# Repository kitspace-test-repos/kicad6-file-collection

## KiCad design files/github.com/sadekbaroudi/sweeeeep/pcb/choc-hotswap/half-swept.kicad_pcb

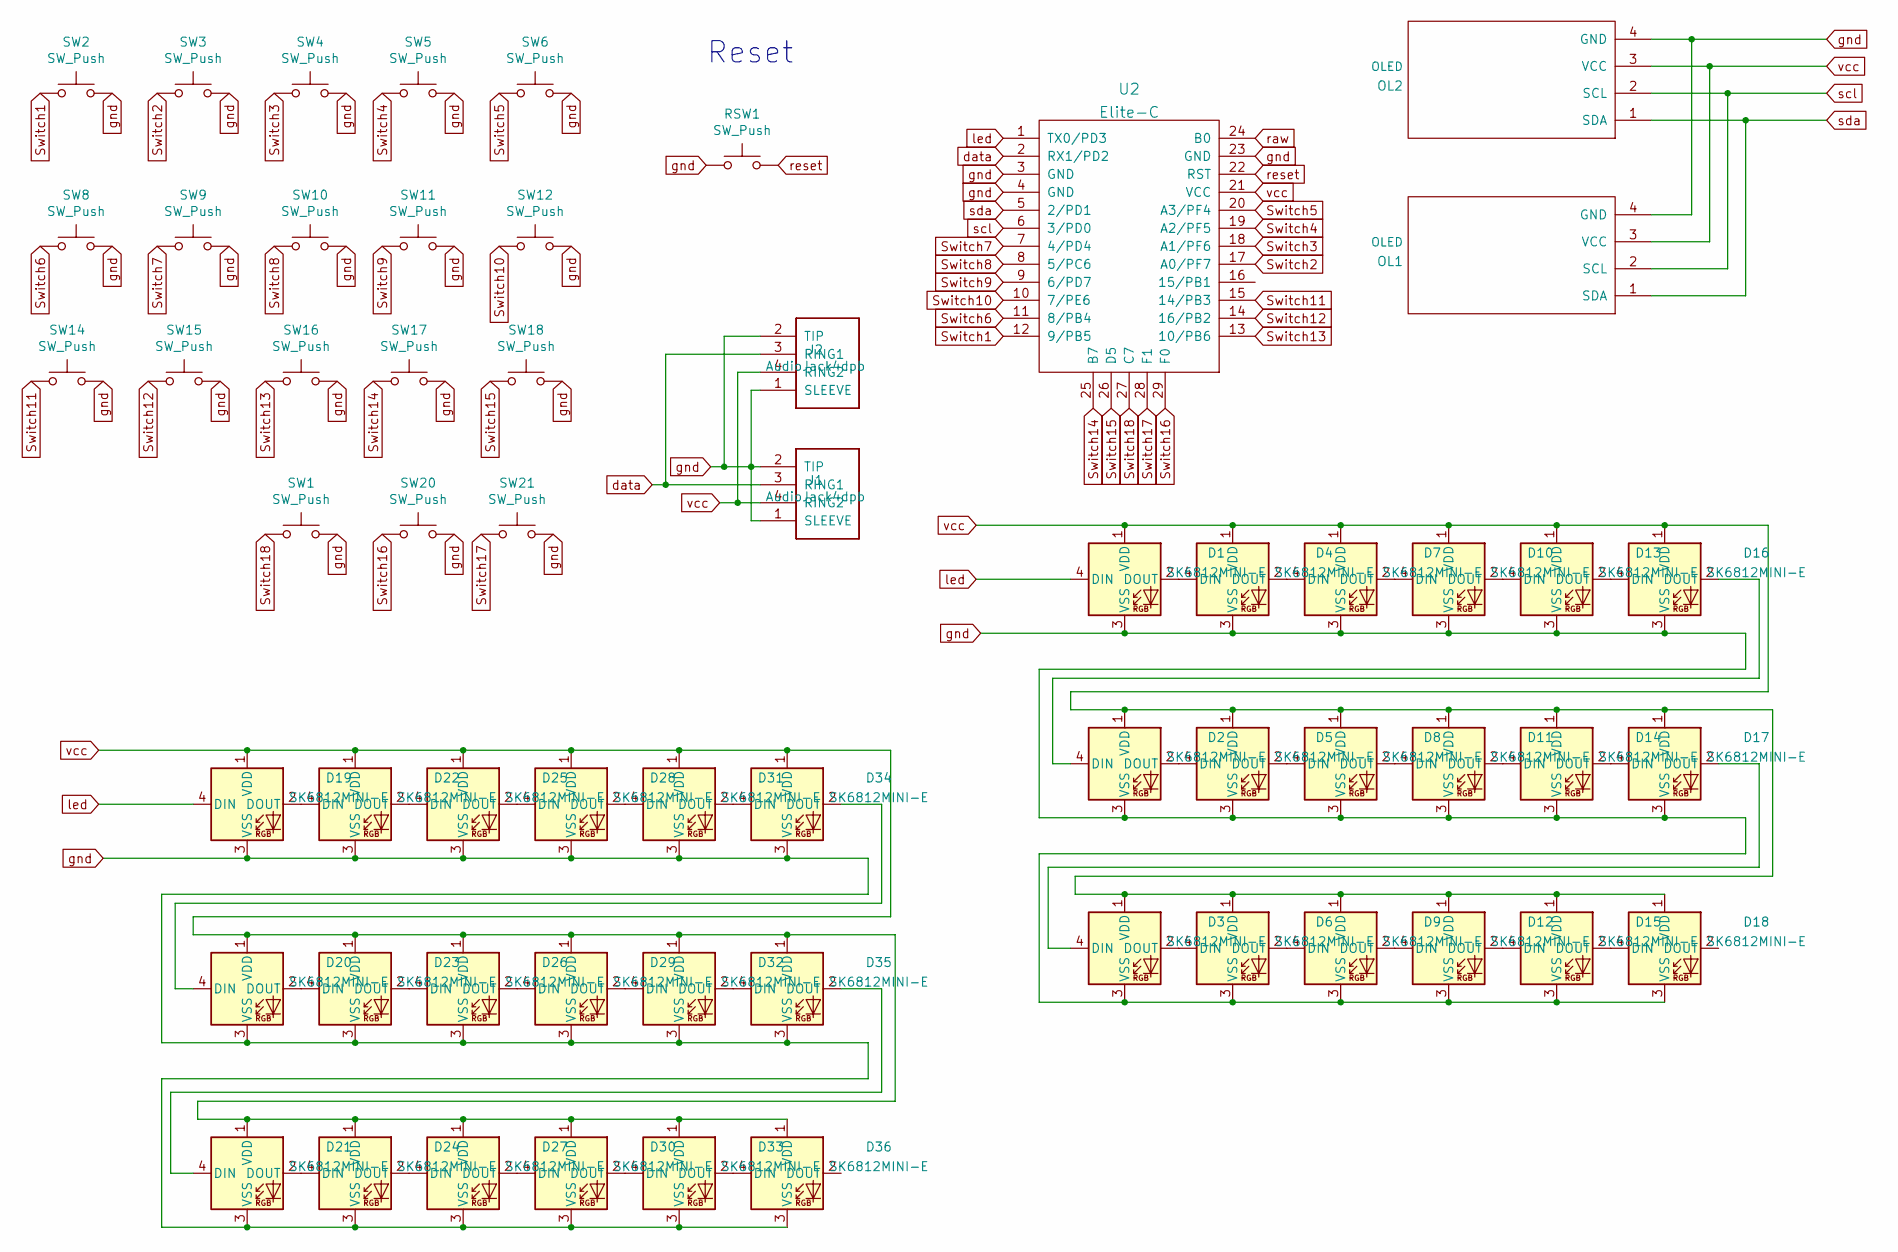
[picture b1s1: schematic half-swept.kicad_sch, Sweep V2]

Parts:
D1, D2, D3, D4, D5, D6, D7, D8, D9, D10, D11, D12, D13, D14, D15, D16, D17, D18, D19, D20, D21, D22, D23, D24, D25, D26, D27, D28, D29, D30, D31, D32, D33, D34, D35, D36: SK6812MINI-E; MX_SK6812MINI-E_REV
J1, J2: AudioJack4dpb; TRRS-PJ-320A
OL1, OL2: OLED; OLED_v2
RSW1: SW_Push; SW_Tactile_SPST_Angled_MJTP1117-no-mount
SW1, SW2, SW3, SW4, SW5, SW6, SW8, SW9, SW10, SW11, SW12, SW14, SW15, SW16, SW17, SW18, SW20, SW21: SW_Push; Kailh_socket_PG1350_reversible
U2: Elite-C

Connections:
unnamed: D1.2 (DOUT), D4.4 (DIN)
unnamed: D2.2 (DOUT), D5.4 (DIN)
unnamed: D3.2 (DOUT), D6.4 (DIN)
unnamed: D4.2 (DOUT), D7.4 (DIN)
unnamed: D5.2 (DOUT), D8.4 (DIN)
unnamed: D6.2 (DOUT), D9.4 (DIN)
unnamed: D10.2 (DOUT), D13.4 (DIN)
unnamed: D7.2 (DOUT), D10.4 (DIN)
unnamed: D11.2 (DOUT), D14.4 (DIN)
unnamed: D8.2 (DOUT), D11.4 (DIN)
unnamed: D12.2 (DOUT), D15.4 (DIN)
unnamed: D9.2 (DOUT), D12.4 (DIN)
unnamed: D13.2 (DOUT), D16.4 (DIN)
unnamed: D14.2 (DOUT), D17.4 (DIN)
unnamed: D15.2 (DOUT), D18.4 (DIN)
unnamed: D2.4 (DIN), D16.2 (DOUT)
unnamed: D3.4 (DIN), D17.2 (DOUT)
unnamed: D19.2 (DOUT), D22.4 (DIN)
unnamed: D20.2 (DOUT), D23.4 (DIN)
unnamed: D20.4 (DIN), D34.2 (DOUT)
unnamed: D21.2 (DOUT), D24.4 (DIN)
unnamed: D21.4 (DIN), D35.2 (DOUT)
unnamed: D22.2 (DOUT), D25.4 (DIN)
unnamed: D23.2 (DOUT), D26.4 (DIN)
unnamed: D24.2 (DOUT), D27.4 (DIN)
unnamed: D25.2 (DOUT), D28.4 (DIN)
unnamed: D26.2 (DOUT), D29.4 (DIN)
unnamed: D27.2 (DOUT), D30.4 (DIN)
unnamed: D28.2 (DOUT), D31.4 (DIN)
unnamed: D29.2 (DOUT), D32.4 (DIN)
unnamed: D30.2 (DOUT), D33.4 (DIN)
unnamed: D31.2 (DOUT), D34.4 (DIN)
unnamed: D32.2 (DOUT), D35.4 (DIN)
unnamed: D33.2 (DOUT), D36.4 (DIN)
Switch1: SW2.1, U2.12 (9/PB5)
Switch2: SW3.1, U2.17 (A0/PF7)
Switch3: SW4.1, U2.18 (A1/PF6)
Switch4: SW5.1, U2.19 (A2/PF5)
Switch5: SW6.1, U2.20 (A3/PF4)
Switch6: SW8.1, U2.11 (8/PB4)
Switch7: SW9.1, U2.7 (4/PD4)
Switch8: SW10.1, U2.8 (5/PC6)
Switch9: SW11.1, U2.9 (6/PD7)
Switch10: SW12.1, U2.10 (7/PE6)
Switch11: SW14.1, U2.15 (14/PB3)
Switch12: SW15.1, U2.14 (16/PB2)
Switch13: SW16.1, U2.13 (10/PB6)
Switch14: SW17.1, U2.25 (B7)
Switch15: SW18.1, U2.26 (D5)
Switch16: SW20.1, U2.29 (F0)
Switch17: SW21.1, U2.28 (F1)
Switch18: SW1.1, U2.27 (C7)
data: J1.3 (RING1), J2.3 (RING1), U2.2 (RX1/PD2)
gnd: D1.3 (VSS), D2.3 (VSS), D3.3 (VSS), D4.3 (VSS), D5.3 (VSS), D6.3 (VSS), D7.3 (VSS), D8.3 (VSS), D9.3 (VSS), D10.3 (VSS), D11.3 (VSS), D12.3 (VSS), D13.3 (VSS), D14.3 (VSS), D15.3 (VSS), D16.3 (VSS), D17.3 (VSS), D18.3 (VSS), D19.3 (VSS), D20.3 (VSS), D21.3 (VSS), D22.3 (VSS), D23.3 (VSS), D24.3 (VSS), D25.3 (VSS), D26.3 (VSS), D27.3 (VSS), D28.3 (VSS), D29.3 (VSS), D30.3 (VSS), D31.3 (VSS), D32.3 (VSS), D33.3 (VSS), D34.3 (VSS), D35.3 (VSS), D36.3 (VSS), J1.1 (SLEEVE), J1.2 (TIP), J2.1 (SLEEVE), J2.2 (TIP), OL1.4 (GND), OL2.4 (GND), RSW1.1, SW1.2, SW2.2, SW3.2, SW4.2, SW5.2, SW6.2, SW8.2, SW9.2, SW10.2, SW11.2, SW12.2, SW14.2, SW15.2, SW16.2, SW17.2, SW18.2, SW20.2, SW21.2, U2.3 (GND), U2.4 (GND), U2.23 (GND)
led: D1.4 (DIN), D19.4 (DIN), U2.1 (TX0/PD3)
raw: U2.24 (B0)
reset: RSW1.2, U2.22 (RST)
scl: OL1.2 (SCL), OL2.2 (SCL), U2.6 (3/PD0)
sda: OL1.1 (SDA), OL2.1 (SDA), U2.5 (2/PD1)
vcc: D1.1 (VDD), D2.1 (VDD), D3.1 (VDD), D4.1 (VDD), D5.1 (VDD), D6.1 (VDD), D7.1 (VDD), D8.1 (VDD), D9.1 (VDD), D10.1 (VDD), D11.1 (VDD), D12.1 (VDD), D13.1 (VDD), D14.1 (VDD), D15.1 (VDD), D16.1 (VDD), D17.1 (VDD), D18.1 (VDD), D19.1 (VDD), D20.1 (VDD), D21.1 (VDD), D22.1 (VDD), D23.1 (VDD), D24.1 (VDD), D25.1 (VDD), D26.1 (VDD), D27.1 (VDD), D28.1 (VDD), D29.1 (VDD), D30.1 (VDD), D31.1 (VDD), D32.1 (VDD), D33.1 (VDD), D34.1 (VDD), D35.1 (VDD), D36.1 (VDD), J1.4 (RING2), J2.4 (RING2), OL1.3 (VCC), OL2.3 (VCC), U2.21 (VCC)

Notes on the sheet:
Reset

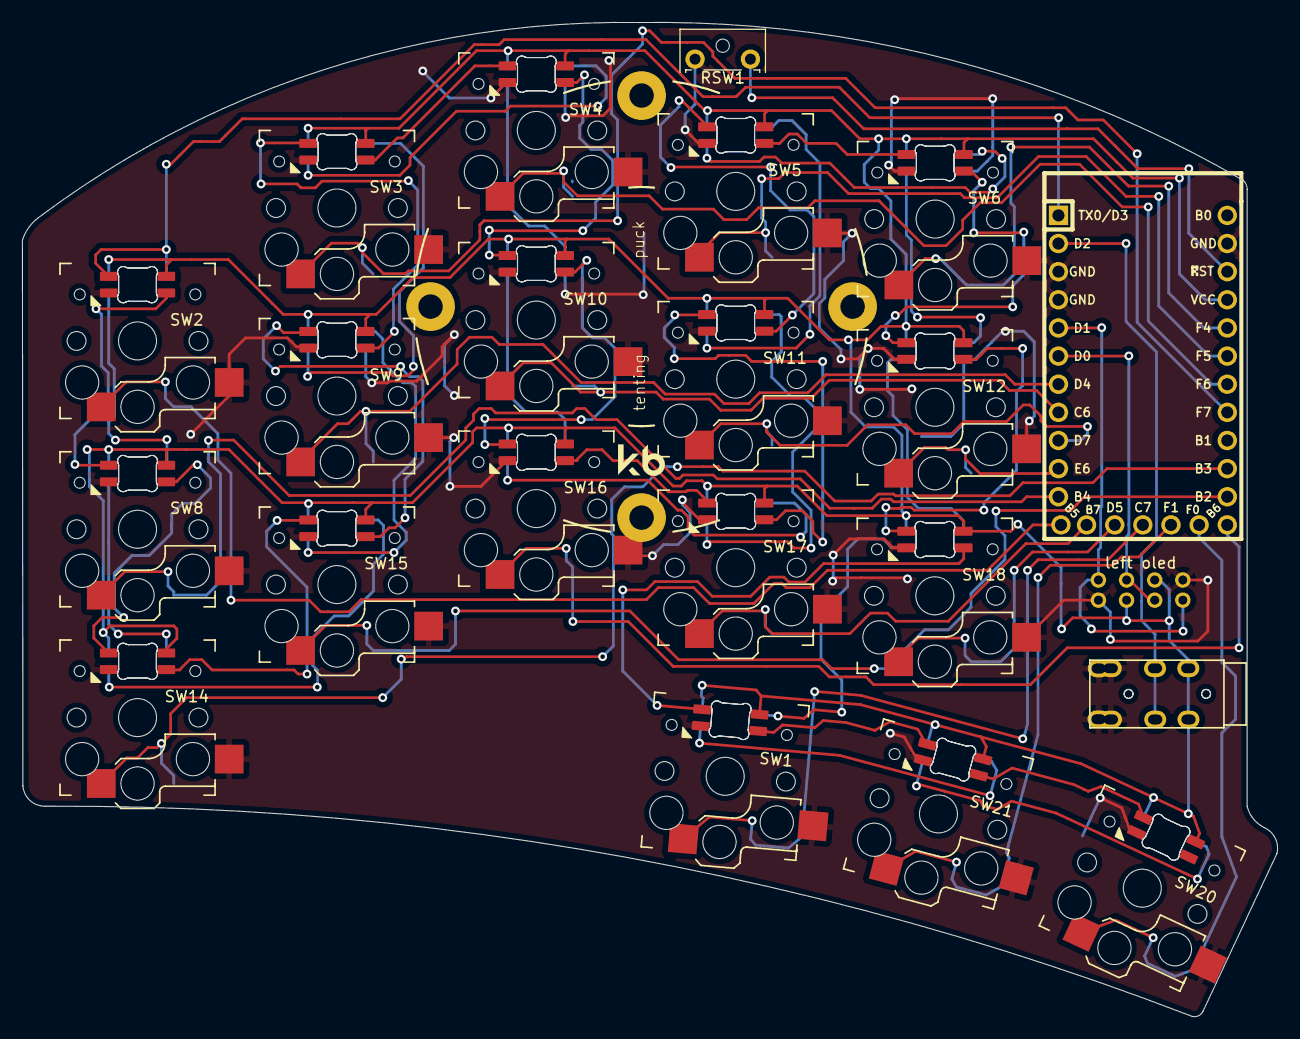
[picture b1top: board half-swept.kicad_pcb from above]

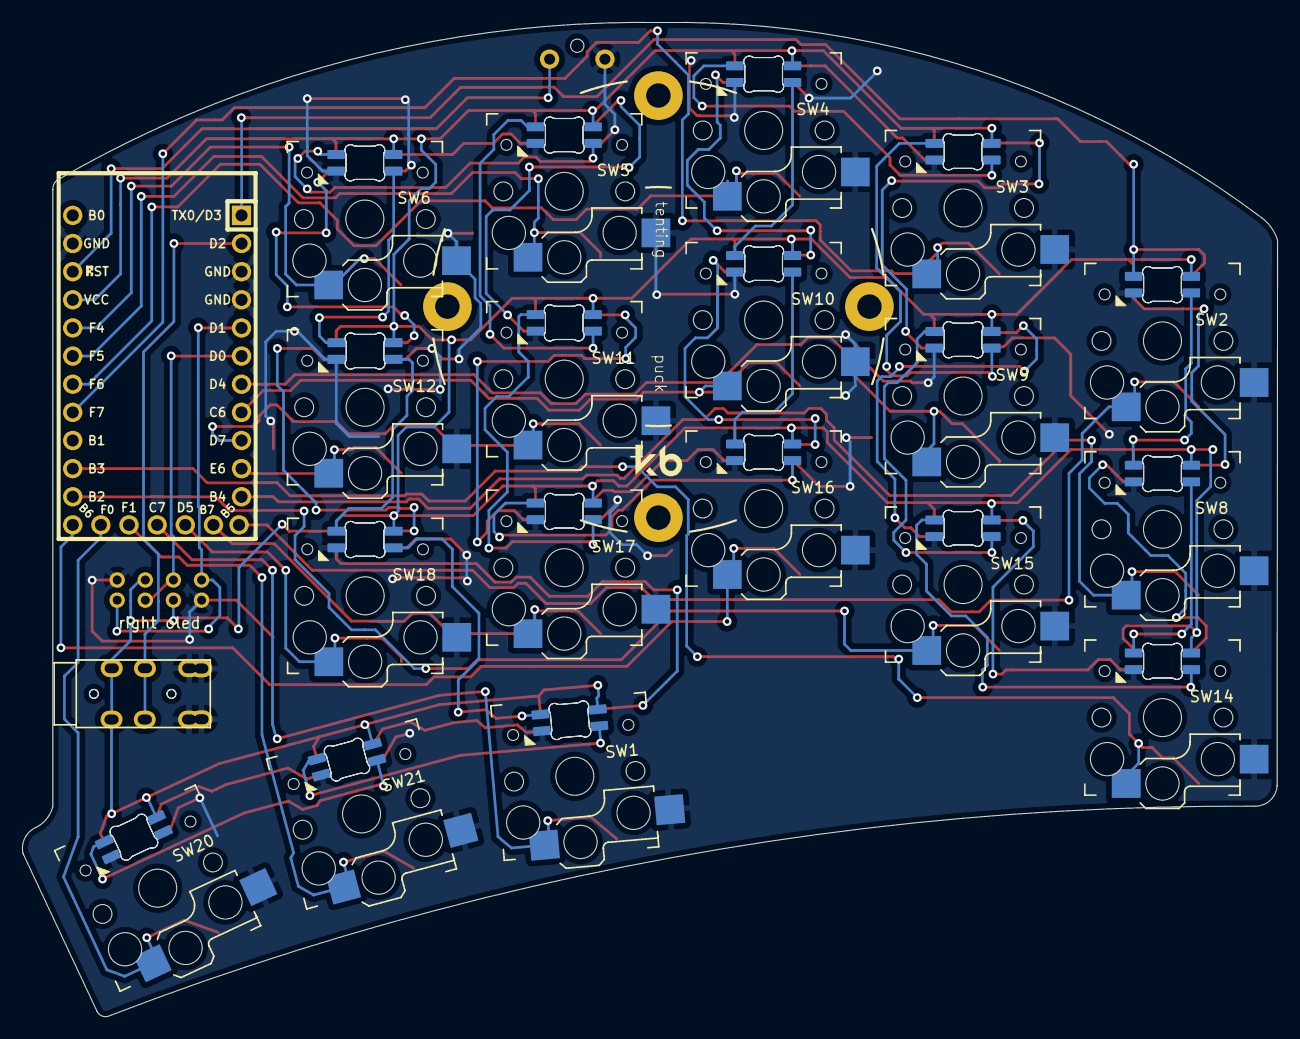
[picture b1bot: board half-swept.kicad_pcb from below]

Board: 2 copper layers, 113.3 x 89.7 mm, 60 parts (20 on the bottom side), 59 nets.

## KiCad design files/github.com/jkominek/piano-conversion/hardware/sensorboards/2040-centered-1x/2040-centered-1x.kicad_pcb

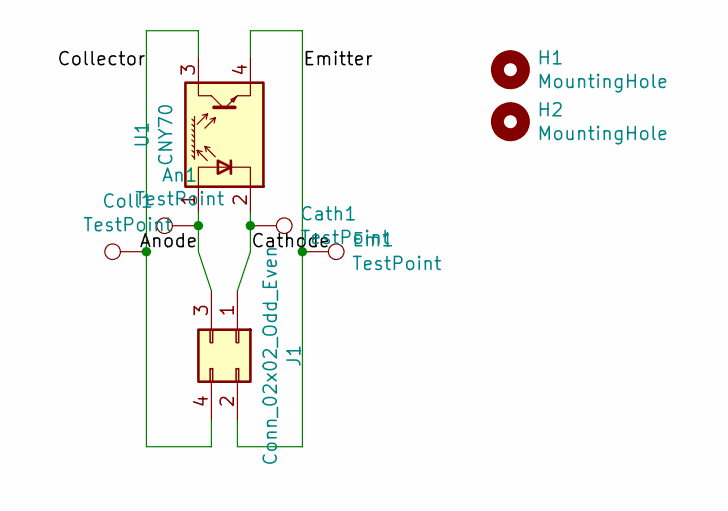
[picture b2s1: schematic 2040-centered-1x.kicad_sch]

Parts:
An1: TestPoint; TestPoint_Pad_1.0x1.0mm
Cath1: TestPoint; TestPoint_Pad_1.0x1.0mm
Coll1: TestPoint; TestPoint_Pad_1.0x1.0mm
Em1: TestPoint; TestPoint_Pad_1.0x1.0mm
H1, H2: MountingHole; MountingHole_3.2mm_M3
J1: Conn_02x02_Odd_Even; Pin_Header_Angled_2x02_Pitch2.54mm
U1: CNY70; Vishay_CNY70

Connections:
/Anode: An1.1, J1.3, U1.1 (A)
/Cathode: Cath1.1, J1.1, U1.2 (K)
/Collector: Coll1.1, J1.4, U1.3 (C)
/Emitter: Em1.1, J1.2, U1.4 (E)

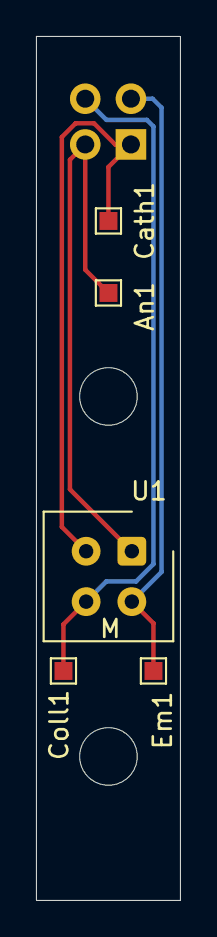
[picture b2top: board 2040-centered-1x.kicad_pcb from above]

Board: 2 copper layers, 8.0 x 48.0 mm, 8 parts (1 on the bottom side), 4 nets.

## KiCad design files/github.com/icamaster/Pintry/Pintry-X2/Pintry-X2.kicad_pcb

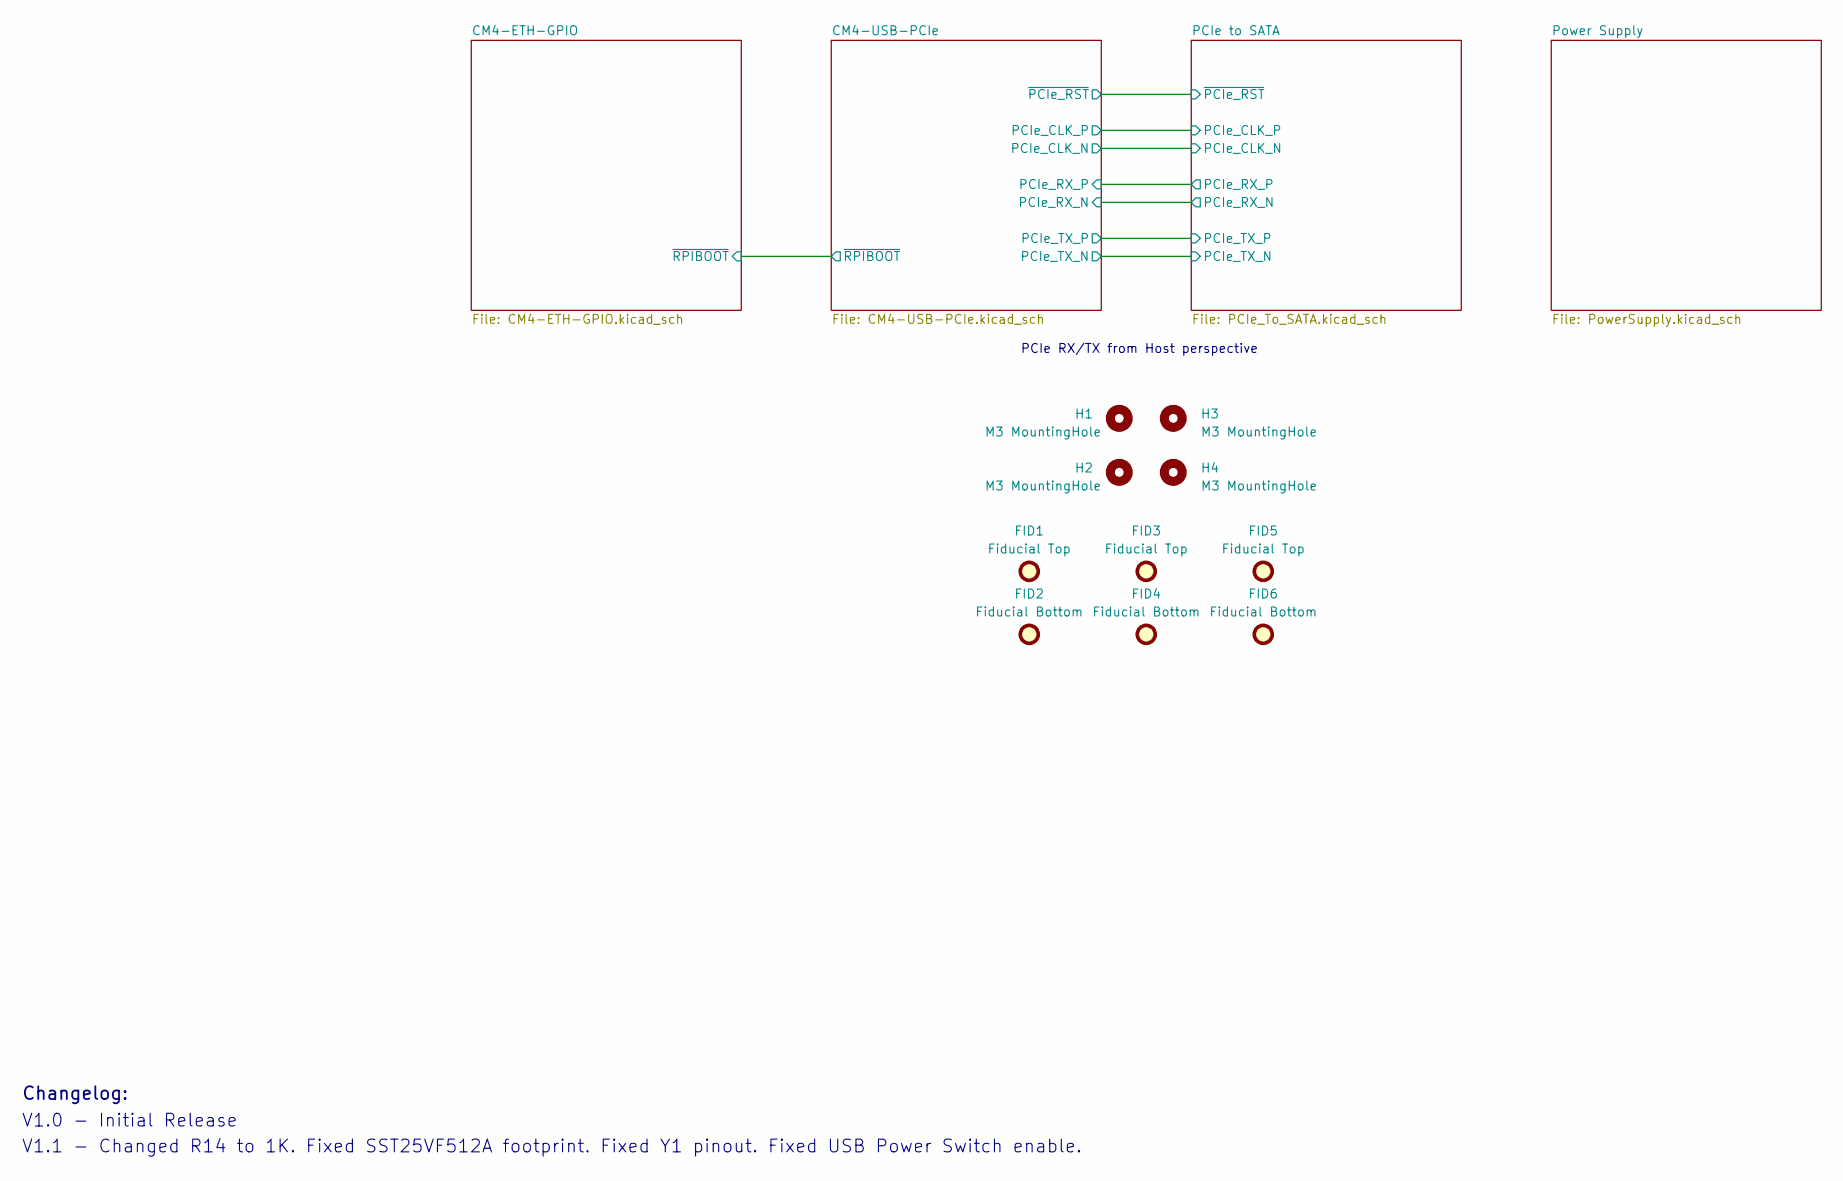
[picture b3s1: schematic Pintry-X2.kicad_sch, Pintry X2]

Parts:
FID1, FID3, FID5: Fiducial Top; Fiducial_1mm_Mask2mm
FID2, FID4, FID6: Fiducial Bottom; Fiducial_1mm_Mask2mm
H1, H2, H3, H4: M3 MountingHole; MountingHole_3.2mm_M3

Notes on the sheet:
V1.0 - Initial Release
Changelog:
PCIe RX/TX from Host perspective
V1.1 - Changed R14 to 1K. Fixed SST25VF512A footprint. Fixed Y1 pinout. Fixed USB Power Switch enable.

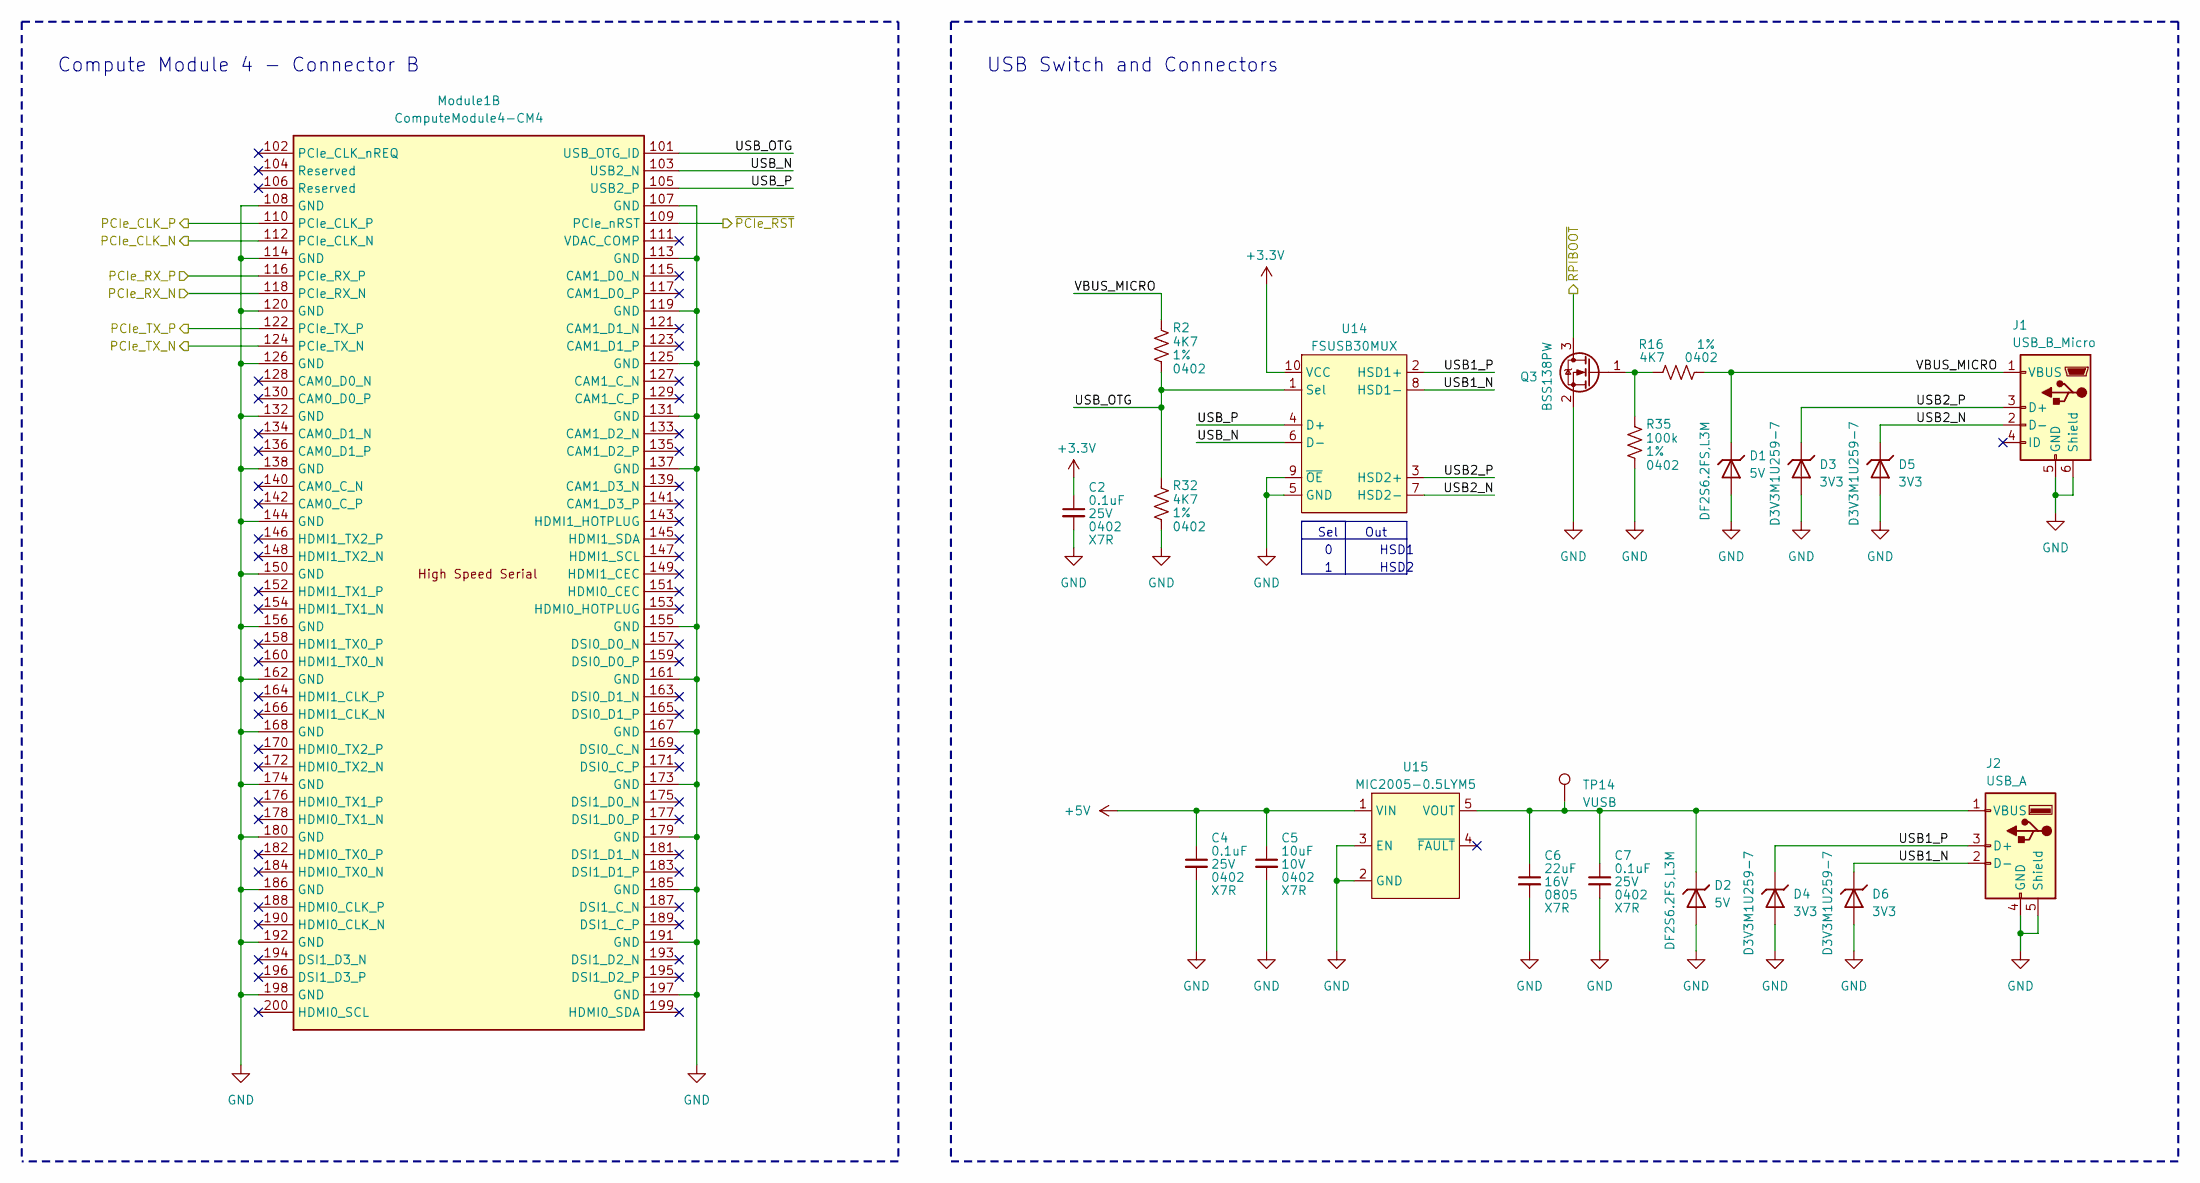
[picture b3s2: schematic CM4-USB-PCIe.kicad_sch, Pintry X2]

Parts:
C2, C4, C7: 0.1uF; C_0402_1005Metric; Voltage Rating 25V
C5: 10uF; C_0402_1005Metric; Voltage Rating 10V
C6: 22uF; C_0805_2012Metric; Voltage Rating 16V; Part Number GRM21BR61A226ME51L
D1, D2: DF2S6.2FS,L3M; D_SOD-923; Part Number DF2S6.2FS,L3M
D3, D4, D5, D6: D3V3M1U259-7; D_SOD-923; Part Number D3V3M1U2S9-7
J1: USB_B_Micro; USB_Micro-B_Amphenol_10103594-0001LF_Horizontal; Part Number 10103594-0001LF
J2: USB_A; USB_A_Amphenol_ICC_73725-11A0BLF_Horizontal; Part Number 73725-11A0BLF
Module1: ComputeModule4-CM4; Raspberry-Pi-4-Compute-Module; Part Number 2x DF40C-100DS-0.4V
Q3: BSS138PW; SOT-323_SC-70; Part Number BSS138PW,115
R2, R16, R32: 4K7; R_0402_1005Metric; Tolerance 1%
R35: 100k; R_0402_1005Metric; Tolerance 1%
TP14: VUSB; TestPoint_Pad_D1.0mm
U14: FSUSB30MUX; MSOP-10_3x3mm_P0.5mm; Part Number FSUSB30MUX
U15: MIC2005-0.5LYM5; SOT-23-5; Part Number MIC2005-0.5LYM5

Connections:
+3V3: C2.1, U14.10 (VCC); also elsewhere on the board
+5V: C4.1, C5.1, U15.1 (VIN); also elsewhere on the board
/CM4-ETH-GPIO/~RPIBOOT: Q3.3 (D); also elsewhere on the board
/CM4-USB-PCIe/PCIe_CLK_N: Module1.112 (PCIe_CLK_N); also elsewhere on the board
/CM4-USB-PCIe/PCIe_CLK_P: Module1.110 (PCIe_CLK_P); also elsewhere on the board
/CM4-USB-PCIe/PCIe_RX_N: Module1.118 (PCIe_RX_N); also elsewhere on the board
/CM4-USB-PCIe/PCIe_RX_P: Module1.116 (PCIe_RX_P); also elsewhere on the board
/CM4-USB-PCIe/PCIe_TX_N: Module1.124 (PCIe_TX_N); also elsewhere on the board
/CM4-USB-PCIe/PCIe_TX_P: Module1.122 (PCIe_TX_P); also elsewhere on the board
/CM4-USB-PCIe/USB1_N: D6.1 (K), J2.2 (D-), U14.8 (HSD1-)
/CM4-USB-PCIe/USB1_P: D4.1 (K), J2.3 (D+), U14.2 (HSD1+)
/CM4-USB-PCIe/USB2_N: D5.1 (K), J1.2 (D-), U14.7 (HSD2-)
/CM4-USB-PCIe/USB2_P: D3.1 (K), J1.3 (D+), U14.3 (HSD2+)
/CM4-USB-PCIe/USB_N: Module1.103 (USB2_N), U14.6 (D-)
/CM4-USB-PCIe/USB_OTG: Module1.101 (USB_OTG_ID), R2.2, R32.1, U14.1 (Sel)
/CM4-USB-PCIe/USB_P: Module1.105 (USB2_P), U14.4 (D+)
/CM4-USB-PCIe/VBUS_MICRO: D1.1 (K), J1.1 (VBUS), R2.1, R16.2
/CM4-USB-PCIe/~PCIe_RST: Module1.109 (PCIe_nRST); also elsewhere on the board
GND: C2.2, C4.2, C5.2, C6.2, C7.2, D1.2 (A), D2.2 (A), D3.2 (A), D4.2 (A), D5.2 (A), D6.2 (A), J1.5 (GND), J1.6 (Shield), J2.4 (GND), J2.5 (Shield), Module1.107 (GND), Module1.108 (GND), Module1.113 (GND), Module1.114 (GND), Module1.119 (GND), Module1.120 (GND), Module1.125 (GND), Module1.126 (GND), Module1.131 (GND), Module1.132 (GND), Module1.137 (GND), Module1.138 (GND), Module1.144 (GND), Module1.150 (GND), Module1.155 (GND), Module1.156 (GND), Module1.161 (GND), Module1.162 (GND), Module1.167 (GND), Module1.168 (GND), Module1.173 (GND), Module1.174 (GND), Module1.179 (GND), Module1.180 (GND), Module1.185 (GND), Module1.186 (GND), Module1.191 (GND), Module1.192 (GND), Module1.197 (GND), Module1.198 (GND), Q3.2 (S), R32.2, R35.2, U14.5 (GND), U14.9 (~OE), U15.2 (GND), U15.3 (EN); also elsewhere on the board
unnamed: C6.1, C7.1, D2.1 (K), J2.1 (VBUS), TP14.1, U15.5 (VOUT)
unnamed: Q3.1 (G), R16.1, R35.1

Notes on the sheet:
Compute Module 4 - Connector B
Sel Out
USB Switch and Connectors
1 HSD2
0 HSD1

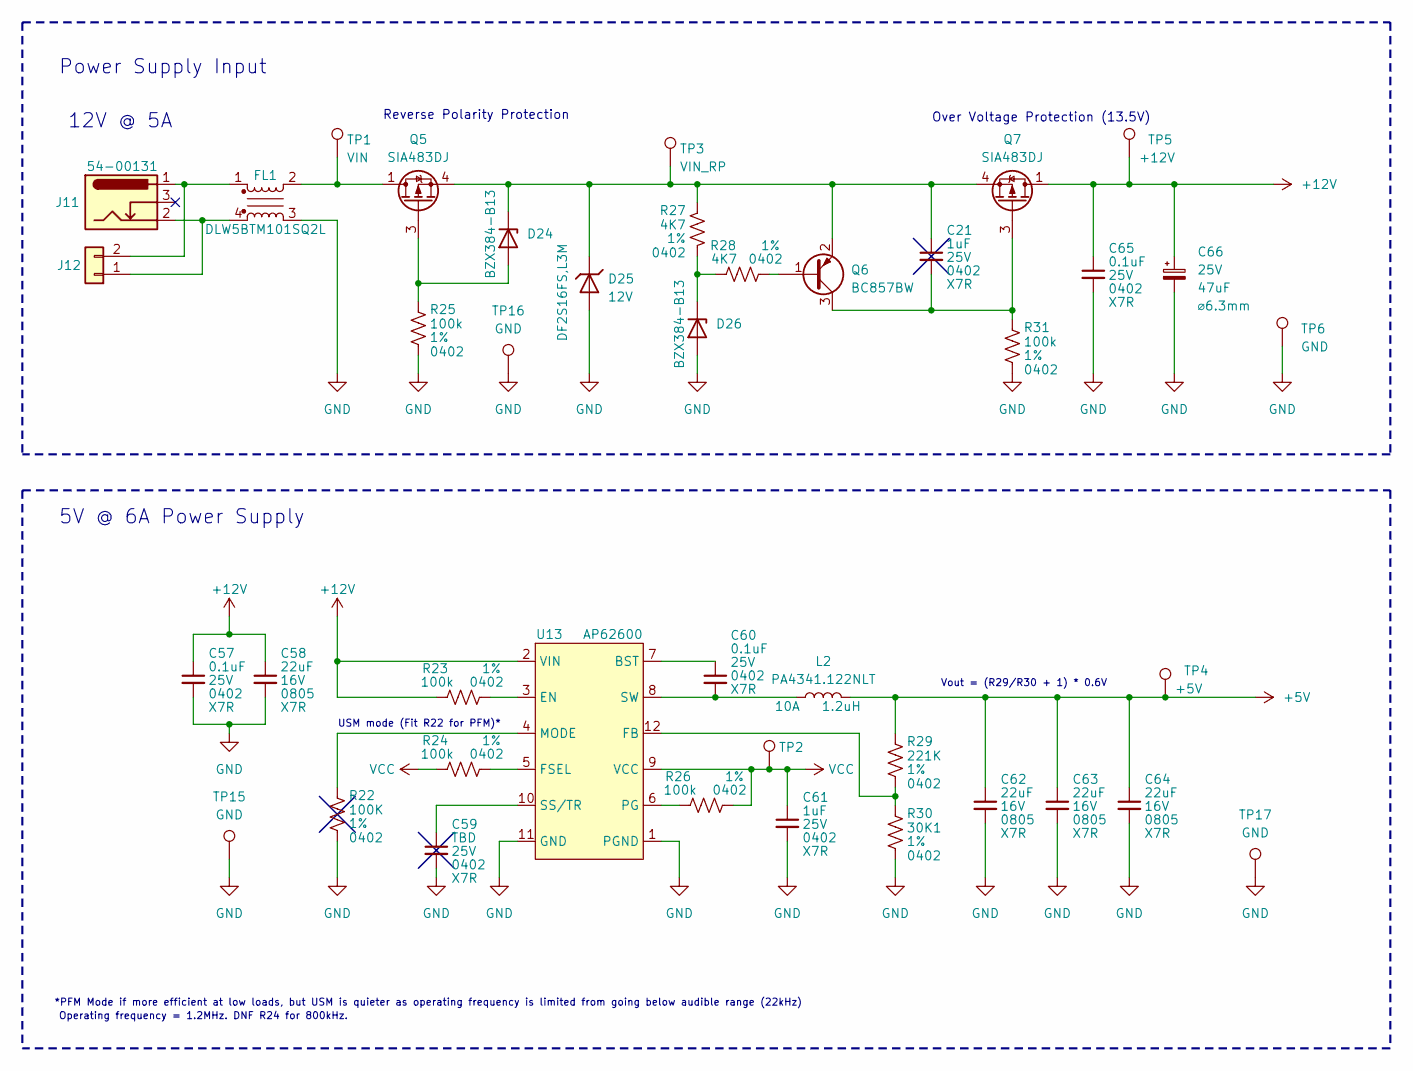
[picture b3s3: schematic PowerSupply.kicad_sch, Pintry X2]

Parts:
C21, C61: 1uF; C_0402_1005Metric; Voltage Rating 25V
C57, C60, C65: 0.1uF; C_0402_1005Metric; Voltage Rating 25V
C58: 22uF; C_0805_2012Metric; Voltage Rating 16V; Part Number CL21A226MOQNNNE
C59: TBD; C_0402_1005Metric; Voltage Rating 25V
C62, C63, C64: 22uF; C_0805_2012Metric; Voltage Rating 16V; Part Number GRM21BR61A226ME51L
C66: 865080443007; CP_Elec_6.3x5.4; Voltage 25V; Part Number 865080443007
D24, D26: BZX384-B13; D_SOD-323; Part Number BZX384-B13,115
D25: DF2S16FS,L3M; D_SOD-923; Part Number DF2S16FS,L3M
FL1: DLW5BTM101SQ2L; Part Number DLW5BTM101SQ2L
J11: 54-00131; Part Number 54-00131
J12: Alternate Power Connector; SolderWire-1sqmm_1x02_P5.4mm_D1.4mm_OD2.7mm
L2: PA4341.122NLT; Pulse_PA4341; Current Rating 10A; Part Number PA4341.122NLT
Q5, Q7: SIA483DJ; Vishay_PowerPAK_SC70-6L_Single; PartNumber SIA483DJ-T1-GE3
Q6: BC857BW; SOT-323_SC-70; Part Number BC857BW,135
R22: 100K; R_0402_1005Metric; Tolerance 1%
R23, R24, R25, R26, R31: 100k; R_0402_1005Metric; Tolerance 1%
R27, R28: 4K7; R_0402_1005Metric; Tolerance 1%
R29: 221K; R_0402_1005Metric; Tolerance 1%
R30: 30K1; R_0402_1005Metric; Tolerance 1%
TP1: VIN; TestPoint_Pad_D1.0mm
TP2: VCC; TestPoint_Pad_D1.0mm
TP3: VIN_RP; TestPoint_Pad_D1.0mm
TP4: +5V; TestPoint_Pad_D1.0mm
TP5: +12V; TestPoint_Pad_D1.0mm
TP6, TP15, TP16, TP17: GND; TestPoint_Pad_D1.0mm
U13: AP62600; V-QFN2030-12 (Type A); Part Number AP62600SJ-7

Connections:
+5V: C62.1, C63.1, C64.1, L2.2, R29.1, TP4.1; also elsewhere on the board
+12V: C57.1, C58.1, C65.1, C66.1, Q7.1 (D), R23.1, TP5.1, U13.2 (VIN); also elsewhere on the board
GND: C57.2, C58.2, C59.2, C61.2, C62.2, C63.2, C64.2, C65.2, C66.2, D25.2 (A), D26.2 (A), FL1.3, R22.2, R25.2, R30.2, R31.2, TP6.1, TP15.1, TP16.1, TP17.1, U13.1 (PGND), U13.11 (GND); also elsewhere on the board
unnamed: C21.1, D24.1 (K), D25.1 (K), Q5.4 (S), Q6.2 (E), Q7.4 (S), R27.1, TP3.1
unnamed: C21.2, Q6.3 (C), Q7.3 (G), R31.1
unnamed: C59.1, U13.10 (SS/TR)
unnamed: C60.1, U13.7 (BST)
unnamed: C60.2, L2.1, U13.8 (SW)
unnamed: D24.2 (A), Q5.3 (G), R25.1
unnamed: D26.1 (K), R27.2, R28.1
unnamed: FL1.1, J11.1 (A), J12.2
unnamed: FL1.2, Q5.1 (D), TP1.1
unnamed: FL1.4, J11.2 (B), J12.1
unnamed: Q6.1 (B), R28.2
unnamed: R22.1, U13.4 (MODE)
unnamed: R23.2, U13.3 (EN)
unnamed: R24.2, U13.5 (FSEL)
unnamed: R26.1, U13.6 (PG)
unnamed: R29.2, R30.1, U13.12 (FB)
VCC: C61.1, R24.1, R26.2, TP2.1, U13.9 (VCC)

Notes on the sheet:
5V @ 6A Power Supply
Power Supply Input
12V @ 5A
USM mode (Fit R22 for PFM)*
Vout = (R29/R30 + 1) * 0.6V
Operating frequency = 1.2MHz. DNF R24 for 800kHz.
*PFM Mode if more efficient at low loads, but USM is quieter as operating frequency is limited from going below audible range (22kHz)
Reverse Polarity Protection
Over Voltage Protection (13.5V)
